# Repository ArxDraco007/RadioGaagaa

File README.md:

# RadioGaagaa
All we hear is radio!!!

## Why I made this - 
I love radios! I have listened to radios ever since I was introduced to it, when I was 10. I listen to old Tamil songs, Tamil is the language spoken in Tamil Nadu, in the southern part of India. Listening to beautiful songs from 4-5 decades ago, truly showed me how beautiful of a time that was. Fallout was my first serious HackClub event, and when I went to a show and tell, people were developing their own radio, since then I wanted to make my own, and I am grateful to HackClub for this opportunity. 

## What was the process-

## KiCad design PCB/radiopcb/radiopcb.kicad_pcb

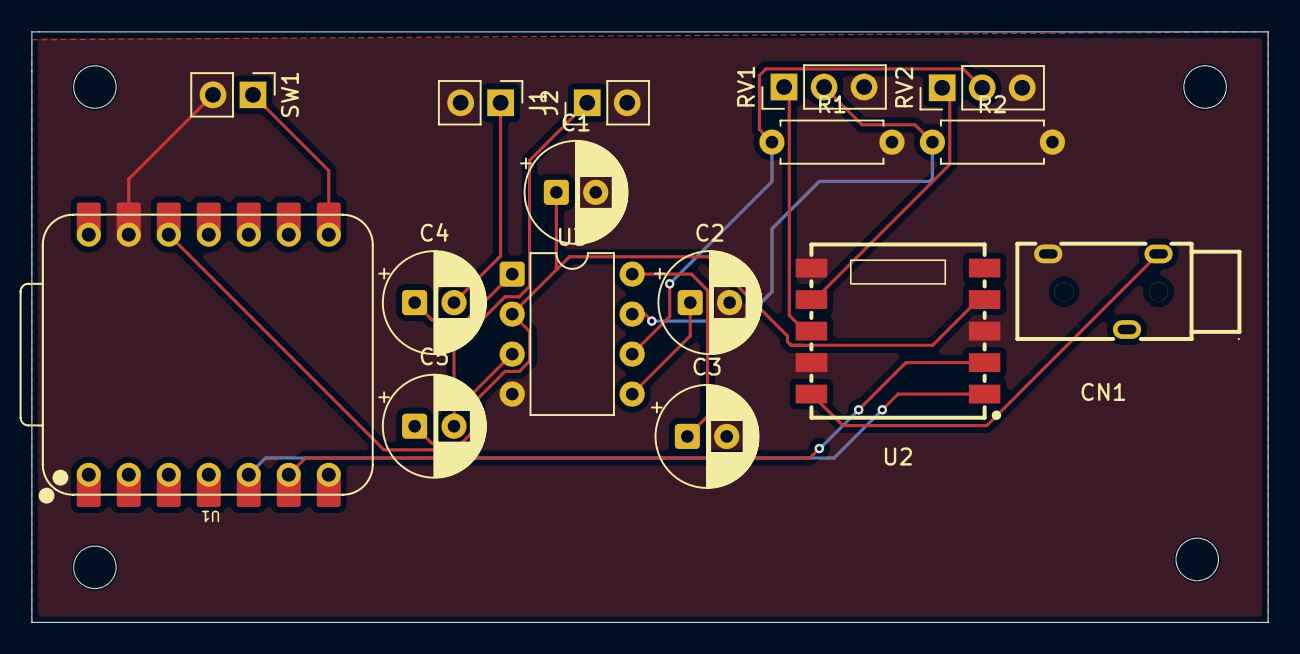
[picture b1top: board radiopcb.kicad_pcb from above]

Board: 2 copper layers, 78.5 x 37.5 mm, 20 parts (0 on the bottom side), 16 nets.

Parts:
C1, C2, C3: 100uF; CP_Radial_D6.3mm_P2.50mm
C4, C5: 470uF; CP_Radial_D6.3mm_P2.50mm
CN1: PJ-3200; AUDIO-TH_PJ-3200
H1, H2, H3, H4: MountingHole; MountingHole_2.7mm_M2.5
J1, J2: Conn_01x02; PinHeader_1x02_P2.54mm_Vertical
R1, R2: R; R_Axial_DIN0207_L6.3mm_D2.5mm_P7.62mm_Horizontal
RV1, RV2: R_Potentiometer; PinHeader_1x03_P2.54mm_Vertical
SW1: PWR; PinHeader_1x02_P2.54mm_Vertical
U1: XIAO-RP2040-DIP
U2: RDA5807MRRD-102V2.0; RDA5807
U3: TDA2822NBD; DIP-8_W7.62mm

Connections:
+3V3: C1.1, U1.12 (3V3), U2.4 (NC), U3.2 (VCC)
/L_AMP_OUT: C5.2, J2.1
/L_OUT: RV2.1, U2.7 (L-OUT)
/R_AMP_OUT: C4.2, J1.1
/R_OUT: RV1.1, U2.8 (R-OUT)
/SCL: U1.6 (GPIO7/SCL), U2.2 (CLK)
/SDA: U1.5 (GPIO6/SDA), U2.1 (DATA)
GND: C1.2, C2.2, C3.2, CN1.4, J1.2, J2.2, R1.2, R2.2, RV1.3, RV2.3, SW1.2, U1.13 (GND), U2.3 (GND), U2.6 (GND), U2.9 (GND), U3.4 (GND)
unnamed: SW1.1, U1.8 (GPIO1/RX)
unnamed: CN1.3, U2.10 (ANT)
unnamed: R2.1, RV1.2, U3.7 (IN1)
unnamed: R1.1, RV2.2, U3.6 (IN2)
unnamed: C3.1, U3.8 (NF1)
unnamed: C2.1, U3.5 (NF2)
unnamed: C4.1, U3.1 (OUT1)
unnamed: C5.1, U3.3 (OUT2)
